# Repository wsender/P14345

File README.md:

Working Repository for P14345
Hybrid Analog and Digital Audio Dynamics Processor

http://edge.rit.edu/edge/P14345/public/Home
======

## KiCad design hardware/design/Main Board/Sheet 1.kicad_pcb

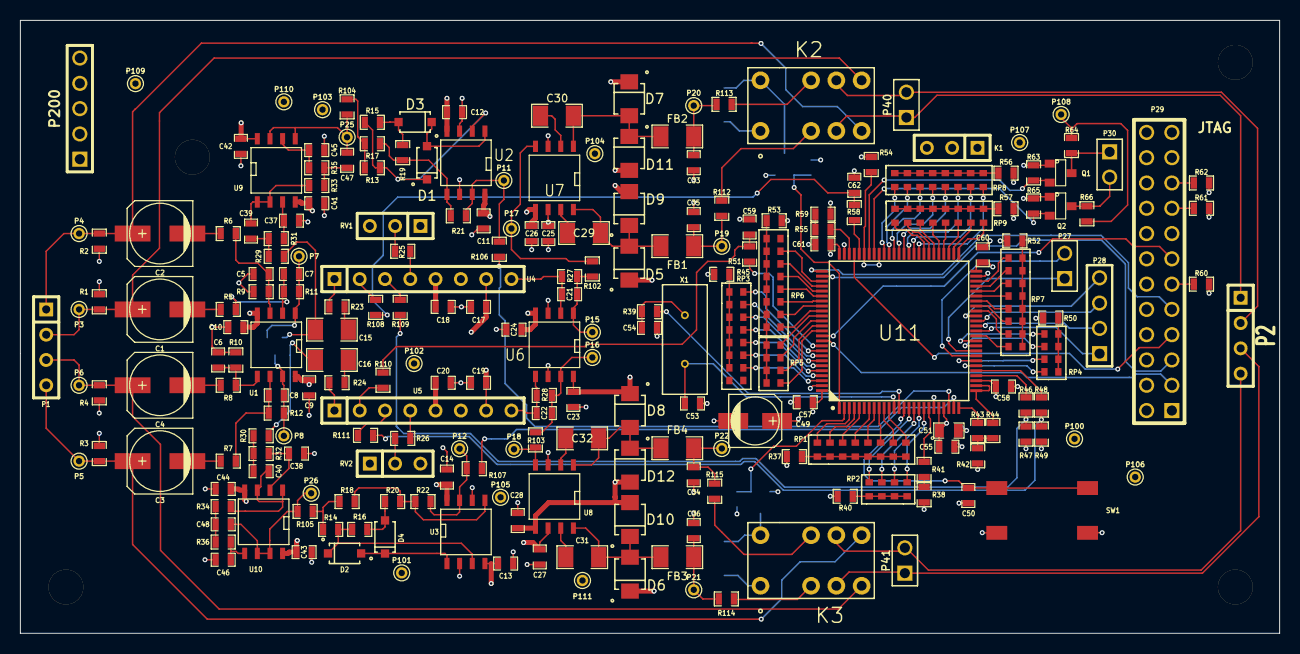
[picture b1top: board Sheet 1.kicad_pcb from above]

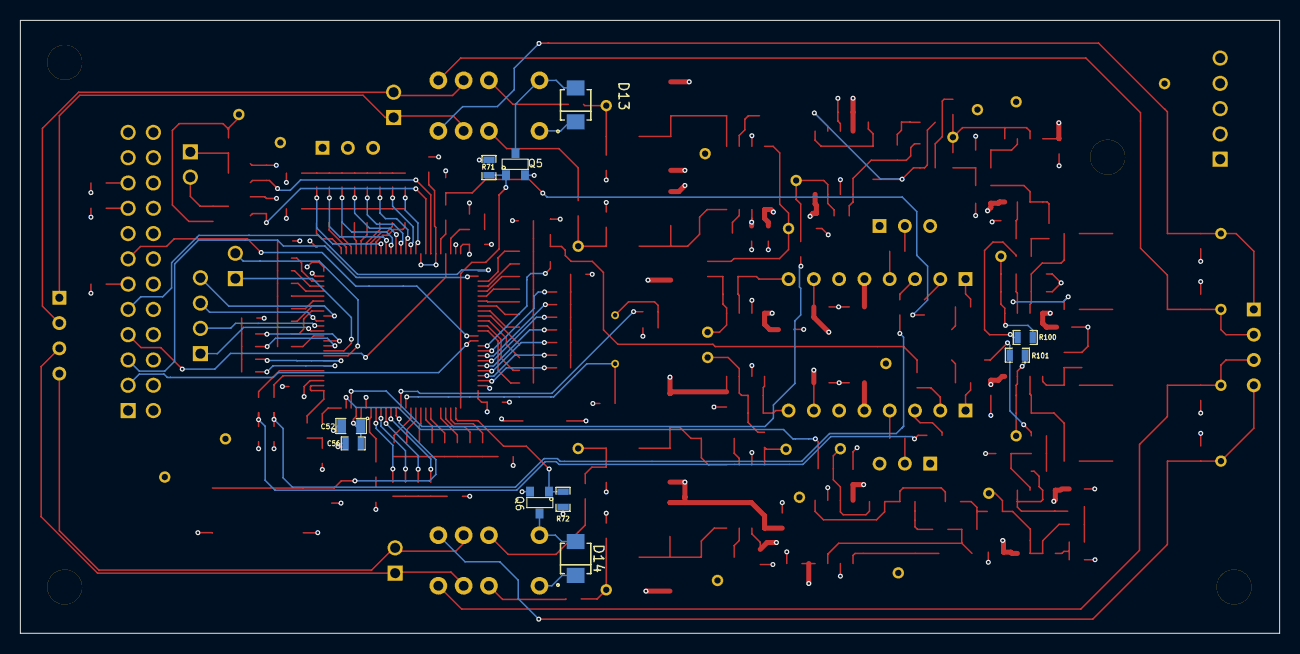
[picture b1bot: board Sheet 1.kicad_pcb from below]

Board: 4 copper layers, 126.5 x 61.6 mm, 238 parts (10 on the bottom side), 193 nets.

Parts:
C1, C2, C3, C4: 22u; c_elec_6.3x5.3
C5, C6, C7, C8: 33p; SM0603_Capa
C9, C10, C11, C12, C13, C14, C17, C18, C19, C20, C23, C24, C25, C26, C27, C28, C41, C42, C43, C44: 0.1u; SM0603_Capa
C15, C16, C29, C30, C31, C32: 10u; SM1206
C21, C22: 22p; SM0603_Capa
C33, C34, C35, C36: 100p; SM0603_Capa
C37, C38: 325p, 5%; SM0603_Capa
C39, C40: 8.47n, 5%; SM0603_Capa
C45, C46: 1.36n, 5%; SM0603_Capa
C47, C48: 13.6n, 5%; SM0603_Capa
C49: 4.7u; c_elec_5x5.3
C50, C55, C56, C57, C58, C59, C60, C61, C62: 100n; SM0603_Capa
C51, C52: 1u; SM0805
C53, C54: 12p; SM0603_Capa
D1, D2, D3, D4: 1N4148; SOD-123
D5, D6, D7, D8, D9, D10, D11, D12: FM4004
D13, D14: DIODE; FM4004
FB1, FB2, FB3, FB4: FILTER; SM1206
K1: CONN_3; SIL-3
K2, K3: PANASONIC_TX-S; 2_FORM_C
M3-HOLE, M3-HOLE#2, M3-HOLE#3, M3-HOLE#4: VAL**; M3-HOLE
P1, P2: CONN_4; SIL-4
P3, P4, P5, P6, P7, P8, P11, P12, P15, P16, P17, P18, P19, P20, P21, P22, P25, P26, P100, P101, P102, P103, P104, P105, P106, P107, P108, P109, P110, P111: TST; PINTST
P27: PROG; PIN_ARRAY_2X1
P28: ROT_ENC; PIN_ARRAY_4x1
P29: JTAG; pin_array_12x2
P30: DISP; PIN_ARRAY_2X1
P40, P41: CONN_2; PIN_ARRAY_2X1
P200: CONN_5; PIN_ARRAY_5x1
Q1, Q2: BSS138; SOT23
Q5, Q6: MMBF170; SOT23
R1, R2, R3, R4, R13, R14, R15, R16, R19, R20, R37, R38, R40, R42, R45, R50, R52, R53, R54, R56, R57, R59, R60, R61, R62, R63, R64, R65, R66, R71, R72: 10K; SM0603_Resistor
R5, R6, R7, R8, R9, R10, R11, R12, R23, R24, R27, R28, R46, R48: 22K; SM0603_Resistor
R17, R18, R21, R22: 20K; SM0603_Resistor
R25, R26: 130K; SM0603_Resistor
R29, R30, R31, R32: 5.11K, 1%; SM0603_Resistor
R33, R34: 691, 1%; SM0603_Resistor
R35, R36: 14.5K, 1%; SM0603_Resistor
R39: 390; SM0603_Resistor
R41, R43, R44, R55, R100, R101, R102, R103, R104, R105, R106, R107, R108, R109, R110, R111, R112, R113: 0; SM0603_Resistor
R47, R49: 1K; SM0603_Resistor
R51, R58: 6.2K; SM0603_Resistor
R114, R115: R; SM0603_Resistor
RP1, RP3, RP6, RP7, RP8, RP9: 0 Ohm; 0603_RN8
RP2, RP4, RP5: 0 Ohm; 0603_RN4
RV1, RV2: 50K; SIL-3
SW1: SW_PUSH; RESET_PB_SW
U1, U2, U3, U6, U9, U10: OP275; SO8N
U4, U5: THAT2181; SIL-8
U7, U8: THAT1646; SO8N
U11: STM32F303XC; LQFP100
X1: 24MHz; ATS

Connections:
+3.3V: C49.1, C51.1, C52.1, C55.1, C56.1, C57.2, C58.2, C60.1, C61.1, D13.2, D14.2, K1.1, K2.1, K3.1, P29.1, P29.2, P106.1, P107.1, P200.5, Q1.1, Q2.1, R63.1, R65.1, U11.21, U11.22, U11.28, U11.50, U11.75, U11.100
+5V: P108.1, P109.1, P200.4, R64.1, R66.1
/Bypass Relays/CH1+: K2.4, P2.1, P40.1
/Bypass Relays/CH1-: K2.9, P2.2, P40.2
/Bypass Relays/CH2+: K3.4, P2.3, P41.1
/Bypass Relays/CH2-: K3.9, P2.4, P41.2
/Bypass Relays/RELAY_1: Q5.1, R71.1, U11.1
/Bypass Relays/RELAY_2: Q6.1, R72.1, U11.2
/Input Section/CH1: C15.1, R29.1, R100.2
/Input Section/CH1+: C2.1, K2.5, P1.1, P4.1, R2.1
/Input Section/CH1-: C1.1, K2.8, P1.2, P3.1, R1.2
/Input Section/CH2: C16.1, R30.1, R101.2
/Input Section/CH2+: C4.1, K3.5, P1.3, P6.1, R4.1
/Input Section/CH2-: C3.1, K3.8, P1.4, P5.1, R3.2
/MCU/A_IN_1: R106.2, U11.23
/MCU/A_IN_2: R107.2, U11.24
/MCU/Bidirectional Level Shift/HV0: P30.1, Q1.3, R64.2
/MCU/Bidirectional Level Shift/HV1: P30.2, Q2.3, R66.2
/MCU/Bidirectional Level Shift/LV0: Q1.2, R63.2, U11.69
/MCU/Bidirectional Level Shift/LV1: Q2.2, R65.2, U11.68
/MCU/CH1_CV: R46.2, R47.1, R109.1
/MCU/CH2_CV: R48.2, R49.1, R111.1
/MCU/JNTRST: P29.3, U11.90
/MCU/JTCK: P29.9, U11.76
/MCU/JTDI: P29.5, U11.77
/MCU/JTDO: P29.13, U11.89
/MCU/JTSM: P29.7, U11.72
/MCU/OSC_IN: C53.2, U11.12, X1.1
/MCU/OSC_OUT: R39.2, U11.13
/Output Stage/CH1+_OUT: K2.3, R112.2
/Output Stage/CH1-_OUT: K2.10, R113.2
/Output Stage/CH1_LN_DVR_IN: P17.1, R102.2, U7.4
/Output Stage/CH2+_OUT: K3.3, R114.2
/Output Stage/CH2-_OUT: K3.10, R115.2
/Output Stage/CH2_LN_DVR_IN: P18.1, R103.2, U8.4
/Precision Rectifier/CH1_RECT_IN: R13.1, R17.1, R104.2
/Precision Rectifier/CH2_RECT_IN: R14.1, R18.1, R105.2
/VCA Section/CH1_CV+: C62.1, R58.2, R108.1
/VCA Section/CH2_CV+: C59.2, R51.2, R110.1
GND: C5.1, C6.1, C9.2, C10.1, C11.2, C12.2, C13.2, C14.2, C17.2, C18.1, C19.2, C20.1, C23.2, C24.2, C25.1, C26.1, C27.1, C28.1, C33.2, C34.2, C35.2, C36.2, C37.1, C38.1, C41.2, C42.2, C43.2, C44.2, C45.1, C46.1, C49.2, C50.1, C51.2, C52.2, C53.1, C54.1, C55.2, C56.2, C57.1, C58.1, C59.1, C60.2, C61.2, C62.2, K1.3, P29.4, P29.6, P29.8, P29.10, P29.12, P29.14, P29.16, P29.18, P29.20, P100.1, P101.1, P102.1, P103.1, P200.1, Q5.2, Q6.2, R1.1, R2.2, R3.1, R4.2, R9.1, R10.1, R37.1, R38.1, R40.1, R42.1, R45.1, R47.2, R49.2, R50.2, R52.2, R53.2, R54.2, R56.2, R57.2, R59.2, R60.2, R61.2, R62.2, R71.2, R72.2, SW1.1, U2.3, U2.6, U3.2, U3.6, U4.6, U5.6, U6.3, U6.6, U7.3, U8.3, U11.20, U11.49, U11.74, U11.99
unnamed: C8.1, P8.1, R12.1, R101.1, U1.7
unnamed: C1.2, R5.1
unnamed: C6.2, R8.2, R10.2, U1.5
unnamed: C8.2, R7.2, R12.2, U1.6
unnamed: C2.2, R6.1
unnamed: C3.2, R7.1
unnamed: C4.2, R8.1
unnamed: C5.2, R6.2, R9.2, U1.3
unnamed: C7.1, P7.1, R11.1, R100.1, U1.1
unnamed: C7.2, R5.2, R11.2, U1.2
unnamed: R18.2, R20.2, R22.1, U3.5
unnamed: P12.1, R22.2, R107.1, U3.7
unnamed: D3.1, R15.2, R19.1
unnamed: D1.2, R13.2, R15.1, U2.2
unnamed: P11.1, R21.2, R106.1, U2.7
unnamed: D1.1, D3.2, U2.1
unnamed: D4.1, R16.2, R20.1
unnamed: D2.1, D4.2, U3.1
unnamed: D2.2, R14.2, R16.1, U3.3
unnamed: R17.2, R19.2, R21.1, U2.5
unnamed: R108.2, U4.2
unnamed: R109.2, U4.3
unnamed: R111.2, U5.3
unnamed: R110.2, U5.2
unnamed: C16.2, R24.1
unnamed: R24.2, U5.1
unnamed: R26.1, U5.4
unnamed: R26.2, RV2.2
unnamed: C22.1, R28.1, U5.8, U6.5
unnamed: C22.2, P16.1, R28.2, R103.1, U6.7
unnamed: C21.1, R27.1, U4.8, U6.2
unnamed: C21.2, P15.1, R27.2, R102.1, U6.1
unnamed: C15.2, R23.1
unnamed: R23.2, U4.1
unnamed: R25.1, U4.4
unnamed: R25.2, RV1.2
unnamed: C30.1, U7.2
unnamed: C32.1, U8.2
unnamed: C31.1, U8.7
unnamed: C36.1, FB3.2, P21.1, R114.1
unnamed: C34.1, FB4.2, P22.1, R115.1
unnamed: C33.1, FB2.2, P20.1, R113.1
unnamed: C35.1, FB1.2, P19.1, R112.1
unnamed: C29.1, U7.7
unnamed: C29.2, D5.1, D9.2, FB1.1, U7.8
unnamed: C30.2, D7.1, D11.2, FB2.1, U7.1
unnamed: C31.2, D6.1, D10.2, FB3.1, U8.8
unnamed: C32.2, D8.1, D12.2, FB4.1, U8.1
unnamed: C38.2, R32.2, U10.2
unnamed: C40.1, R30.2, R32.1
unnamed: C46.2, R36.2, U10.5
unnamed: C48.1, R34.2, R36.1
unnamed: C48.2, P26.1, R105.1, U10.6, U10.7
unnamed: C40.2, R34.1, U10.1, U10.3
unnamed: C37.2, R31.2, U9.3
unnamed: C39.1, R29.2, R31.1
unnamed: C45.2, R35.2, U9.6
unnamed: C47.1, R33.2, R35.1
unnamed: C39.2, R33.1, U9.1, U9.2
unnamed: C47.2, P25.1, R104.1, U9.5, U9.7
unnamed: RP6.12, U11.80
unnamed: P29.19, R62.1
unnamed: P29.17, R61.1
unnamed: P29.11, R60.1
unnamed: RP6.11, U11.79
unnamed: RP1.4, U11.7
unnamed: RP1.5, U11.8
unnamed: RP1.6, U11.9
unnamed: P28.1, U11.38
unnamed: RP1.7, U11.10
unnamed: RP1.8, U11.11
unnamed: RP6.15, U11.83
unnamed: RP6.16, U11.84
unnamed: RP6.10, U11.78
unnamed: RP4.1, U11.31
unnamed: RP7.1, U11.37
unnamed: RP4.3, U11.35
unnamed: RP6.14, U11.82
unnamed: RP1.3, U11.5
unnamed: RP1.2, U11.4
unnamed: RP1.1, U11.3
unnamed: R37.2, RP1.9, RP1.10, RP1.11, RP1.12, RP1.13, RP1.14, RP1.15, RP1.16
unnamed: C50.2, SW1.2, U11.14
unnamed: R45.2, RP3.10, RP3.11, RP3.12, RP3.13, RP3.14, RP3.15, RP3.16
unnamed: R43.1, U11.25
unnamed: R44.1, U11.26, U11.27
unnamed: R55.2, U11.73
unnamed: RP7.2, U11.42
unnamed: RP7.8, U11.48
unnamed: RP7.3, U11.43
unnamed: RP5.5, U11.85
unnamed: RP5.6, U11.86
unnamed: RP5.7, U11.87
unnamed: RP5.8, U11.88
unnamed: R48.1, U11.30
unnamed: P28.2, U11.39
unnamed: P28.3, U11.40
unnamed: P28.4, U11.41
unnamed: R46.1, U11.29
unnamed: R58.1, U11.71
unnamed: R51.1, U11.91
unnamed: R50.1, RP4.5, RP4.6, RP4.7, RP4.8
unnamed: RP6.13, U11.81
unnamed: RP7.7, U11.47
unnamed: RP7.6, U11.46
unnamed: RP7.5, U11.45
unnamed: RP7.4, U11.44
unnamed: R52.1, RP7.9, RP7.10, RP7.11, RP7.12, RP7.13, RP7.14, RP7.15, RP7.16
unnamed: RP3.7, U11.98
unnamed: RP3.6, U11.97
unnamed: R42.2, R43.2, R44.2
unnamed: R53.1, RP5.1, RP5.2, RP5.3, RP5.4, RP6.1, RP6.2, RP6.3, RP6.4, RP6.5, RP6.6, RP6.7, RP6.8
unnamed: R55.1, R59.1
unnamed: RP3.1, U11.92
unnamed: RP3.2, U11.93
unnamed: RP3.3, U11.94
unnamed: RP3.4, U11.95
unnamed: RP3.5, U11.96
unnamed: RP9.16, U11.58
unnamed: RP9.15, U11.57
unnamed: RP9.14, U11.56
unnamed: RP9.13, U11.55
unnamed: RP9.12, U11.54
unnamed: RP9.11, U11.53
unnamed: RP9.10, U11.52
unnamed: RP9.9, U11.51
unnamed: RP2.1, U11.15
unnamed: RP2.2, U11.16
unnamed: RP2.3, U11.17
unnamed: RP2.4, U11.18
unnamed: R57.1, RP9.1, RP9.2, RP9.3, RP9.4, RP9.5, RP9.6, RP9.7, RP9.8
unnamed: R40.2, RP2.5, RP2.6, RP2.7, RP2.8
unnamed: R41.1, U11.19
unnamed: R38.2, R41.2
unnamed: RP4.2, U11.32
unnamed: RP4.4, U11.36
unnamed: P27.2, U11.33
unnamed: P27.1, U11.34
unnamed: R54.1, U11.67, U11.70
unnamed: RP8.9, U11.59
unnamed: RP8.10, U11.60
unnamed: RP8.11, U11.61
unnamed: RP8.12, U11.62
unnamed: RP8.13, U11.63
unnamed: RP8.14, U11.64
unnamed: RP8.15, U11.65
unnamed: RP8.16, U11.66
unnamed: R56.1, RP8.1, RP8.2, RP8.3, RP8.4, RP8.5, RP8.6, RP8.7, RP8.8
unnamed: C54.2, R39.1, X1.2
unnamed: D13.1, K2.12, Q5.3
unnamed: D14.1, K3.12, Q6.3
VDD: C9.1, C11.1, C13.1, C17.1, C19.1, C23.1, C25.2, C27.2, C42.1, C44.1, D5.2, D6.2, D7.2, D8.2, P110.1, P111.1, P200.2, RV1.3, RV2.3, U1.8, U2.8, U3.4, U4.7, U5.7, U6.8, U7.6, U8.6, U9.8, U10.4
VSS: C10.2, C12.1, C14.1, C18.2, C20.2, C24.1, C26.2, C28.2, C41.1, C43.1, D9.1, D10.1, D11.1, D12.1, P104.1, P105.1, P200.3, RV1.1, RV2.1, U1.4, U2.4, U3.8, U4.5, U5.5, U6.4, U7.5, U8.5, U9.4, U10.8

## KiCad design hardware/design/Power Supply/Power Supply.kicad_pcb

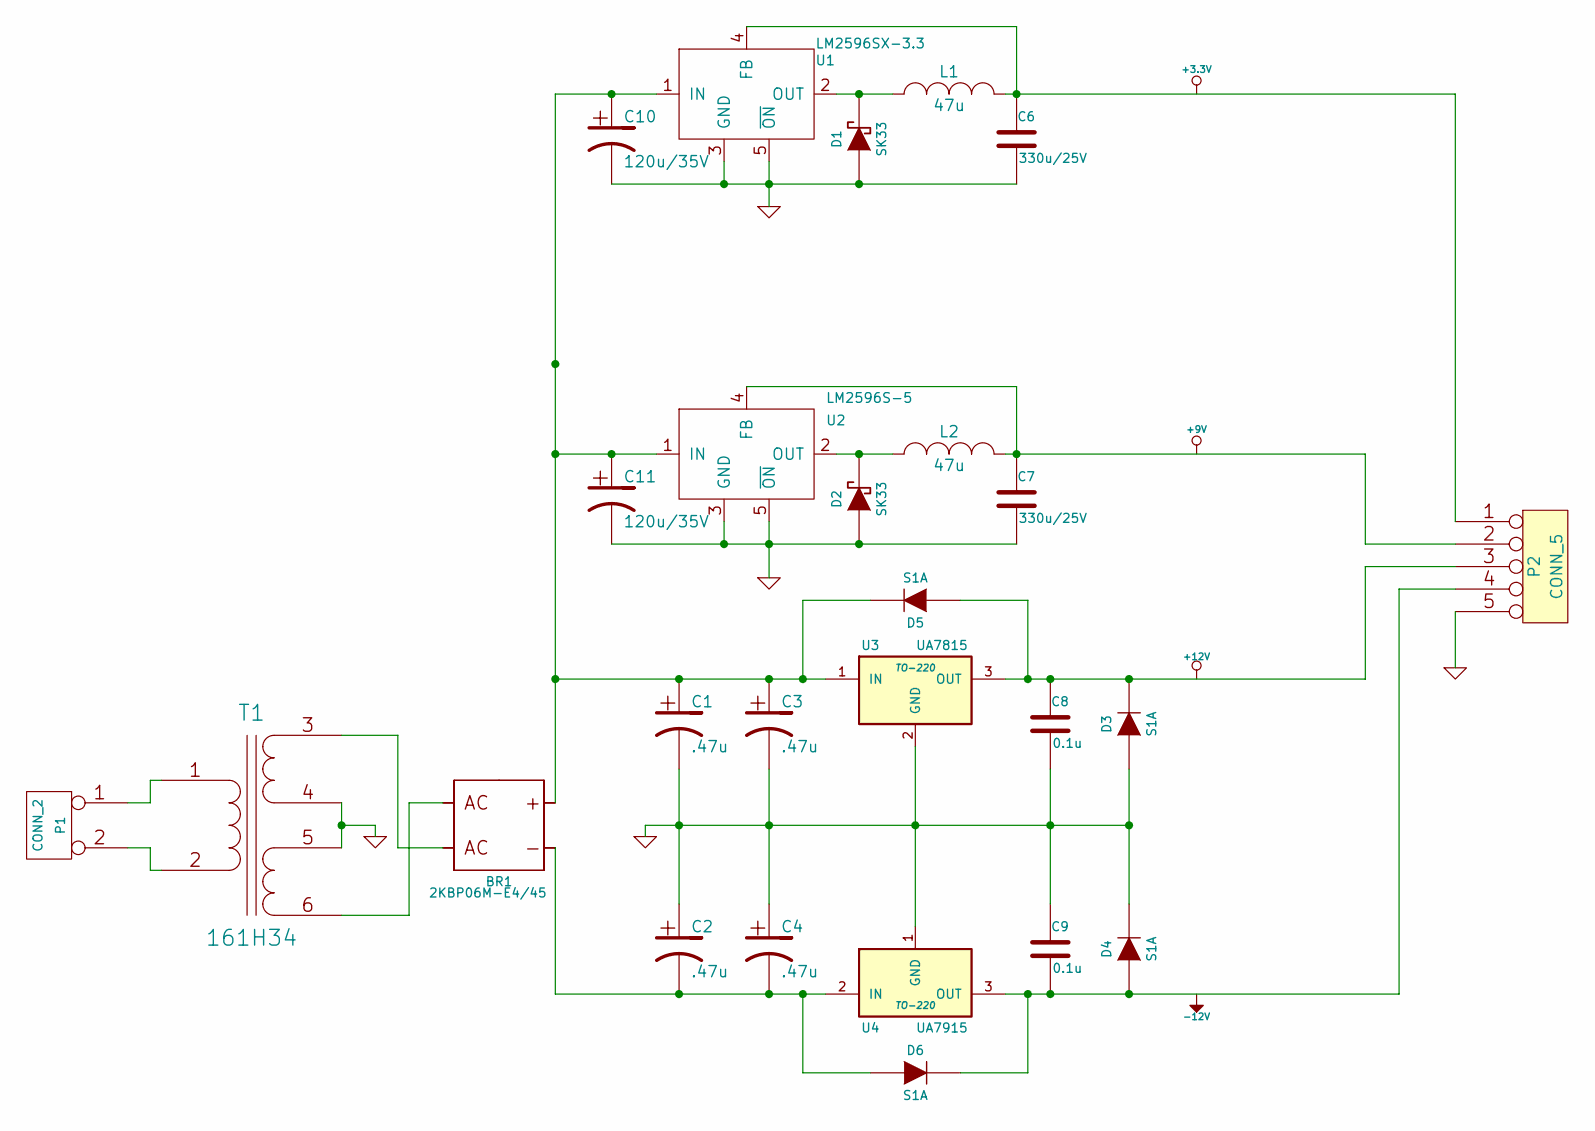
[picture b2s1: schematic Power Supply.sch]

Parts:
BR1: 2KBP06M-E4/45
C1, C2, C3, C4: .47u
C6, C7: 330u/25V
C8, C9: 0.1u
C10, C11: 120u/35V
D1, D2: SK33
D3, D4, D5, D6: S1A
L1, L2: 47u
P1: CONN_2
P2: CONN_5
T1: 161H34
U1: LM2596SX-3.3
U2: LM2596S-5
U3: UA7815; TO-220
U4: UA7915; TO-220

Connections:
GND: C1.2, C2.1, C3.2, C4.1, C6.2, C7.2, C8.2, C9.1, C10.2, C11.2, D1.1 (A), D2.1 (A), D3.1 (A), D4.2 (K), P2.5, T1.4 (SB), T1.5 (SC), U1.3 (GND), U1.5 (~ON), U2.3 (GND), U2.5 (~ON), U3.2 (GND), U4.1 (GND)
unnamed: P1.1, T1.1 (AA)
unnamed: P1.2 (PM), T1.2 (AB)
unnamed: C6.1, L1.2, P2.1, U1.4 (FB)
unnamed: C8.1, D3.2 (K), D5.1 (A), P2.3, U3.3 (OUT)
unnamed: C9.2, D4.1 (A), D6.2 (K), P2.4, U4.3 (OUT)
unnamed: C7.1, L2.2, P2.2, U2.4 (FB)
unnamed: BR1.3 (AC_IN), T1.3 (SA)
unnamed: BR1.2 (AC_IN), T1.6 (SD)
unnamed: D2.2 (K), L2.1, U2.2 (OUT)
unnamed: BR1.4 (NEG), C2.2, C4.2, D6.1 (A), U4.2 (IN)
unnamed: BR1.1 (POS), C1.1, C3.1, C10.1, C11.1, D5.2 (K), U1.1 (IN), U2.1 (IN), U3.1 (IN)
unnamed: D1.2 (K), L1.1, U1.2 (OUT)

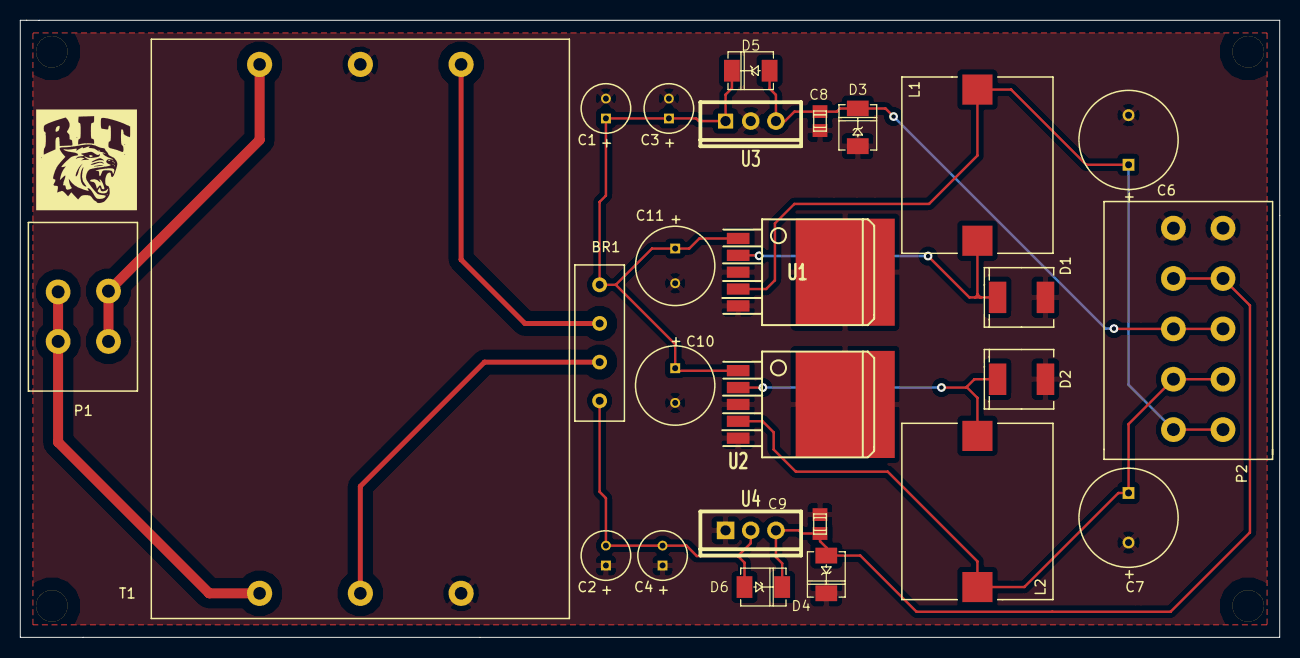
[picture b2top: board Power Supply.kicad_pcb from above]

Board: 2 copper layers, 127.0 x 62.2 mm, 31 parts (0 on the bottom side), 13 nets.

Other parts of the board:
4-40, 4-40#2, 4-40#3, 4-40#4: VAL**; 4-40
VIA_OSHPARK: VAL**; VIA_OSHPARK

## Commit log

2014-04-02 Initialization
    Adding some reference resources to project.
2014-04-02 added readme in software directory
2014-04-03 Parts Order
    Parts order for VCA testing and Microcontroller Development board.
2014-04-06 Support Materials
    Start a BOM and a Current Calculator (for power supply design).
2014-04-06 Version Correction
2014-04-07 Power Supply Design
    Power Supply schematic capture as well as creation of P14345 custom
    parts library for KiCAD.
2014-04-11 Delete 4-4-14 Order.xlsx
    Trying to resolve conflicts....
2014-04-14 Power Supply Design
    First Pass at Power Supply PCB design
2014-04-14 Power Supply Design
    Finished board routing and Gerber generation.
2014-04-14 Power Supply Design
    Working update. Changing 9V rail to 5V.
2014-04-15 Power Supply Design
    Version 0.1 - Pilot release for review
2014-04-16 Main PCB Design
    Started Design of Main PCB
2014-04-16 Update
    Update
2014-04-16 Main PCB Design
    Added VCA Section and required materials
2014-04-17 Conflict Resolution
    Fixed, hopefully
2014-04-17 Main PCB Design
    Added Output Stage
2014-04-29 Added Power Ports
2014-05-02 Op Amp Changes
2014-05-04 Sheet 7 Creation
    Started sheet for MCU
2014-05-06 MCU Work
2014-05-11 Version 1.0
    Wrapped up design. Version for Detailed Design Review.
2014-05-11 Version 1.0.05112014.1736
    Updated Sheet Sizes
    Added Voltage Divider
2014-05-15 Version 1.0.051414.2106
    - Added JTAG & Programming Port to MCU.
    - Moved I2C Display to the I2C2 Buss.
    - Added 10K reference resistors.
2014-08-26 Version 1.0.082514.2134
    Initial partial PCB layout.
2014-09-02 Version 1.0.090114.2238
    Completed Layout
2014-09-09 Version 1.0.090814.2105
    Gerbers
2014-09-18 Add
    Adding attrel files for all to see. I am moving to UI now.
2014-09-22 High Level UI
    First revision, in progress
2014-09-25 Jeff: software
2014-09-27 Blank Project Template
2014-09-27 STM32 Keil Guide
    Keil setup to run the STM32F3 Discovery board
2014-09-30 added UI functions
2014-09-30 9.30.14
2014-10-02 10.2.14
